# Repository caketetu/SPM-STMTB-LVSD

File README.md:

# STM32C092KBT6 Project

## 概要

STM32C092KBT6を使用した組み込み制御プロジェクト。

各種通信、タイマー、PWM、LED、モーター制御などの機能を実装する。

## 機能

* GPIO制御
* UART通信
* CAN通信
* タイマー割り込み
* PWM出力
* RGB LED制御
* Flashパラメータ保存

## ピン配置

| Pin  | Function  |
| ---- | --------- |
| PA11 | FDCAN1_RX |
| PB1  | FDCAN1_TX |
| PB7  | USART1_RX |
| PC14 | USART1_TX |
| PA8  | TIM1_CH1  |

## 開発環境

| 項目       | 内容                      |
| -------- | ----------------------- |
| MCU      | STM32C092KBT6           |
| IDE      | STM32CubeIDE for VSCode |
| CubeMX   | STM32CubeMX 6.15.0      |
| Firmware | STM32CubeC0             |
| Language | C                       |

## 実装予定機能

* [ ] CAN通信
* [ ] モーター制御
* [ ] 加減速制御
* [ ] Flashパラメータ管理
* [ ] RGB LED制御
* [ ] エラー処理
* [ ] ウォッチドッグ

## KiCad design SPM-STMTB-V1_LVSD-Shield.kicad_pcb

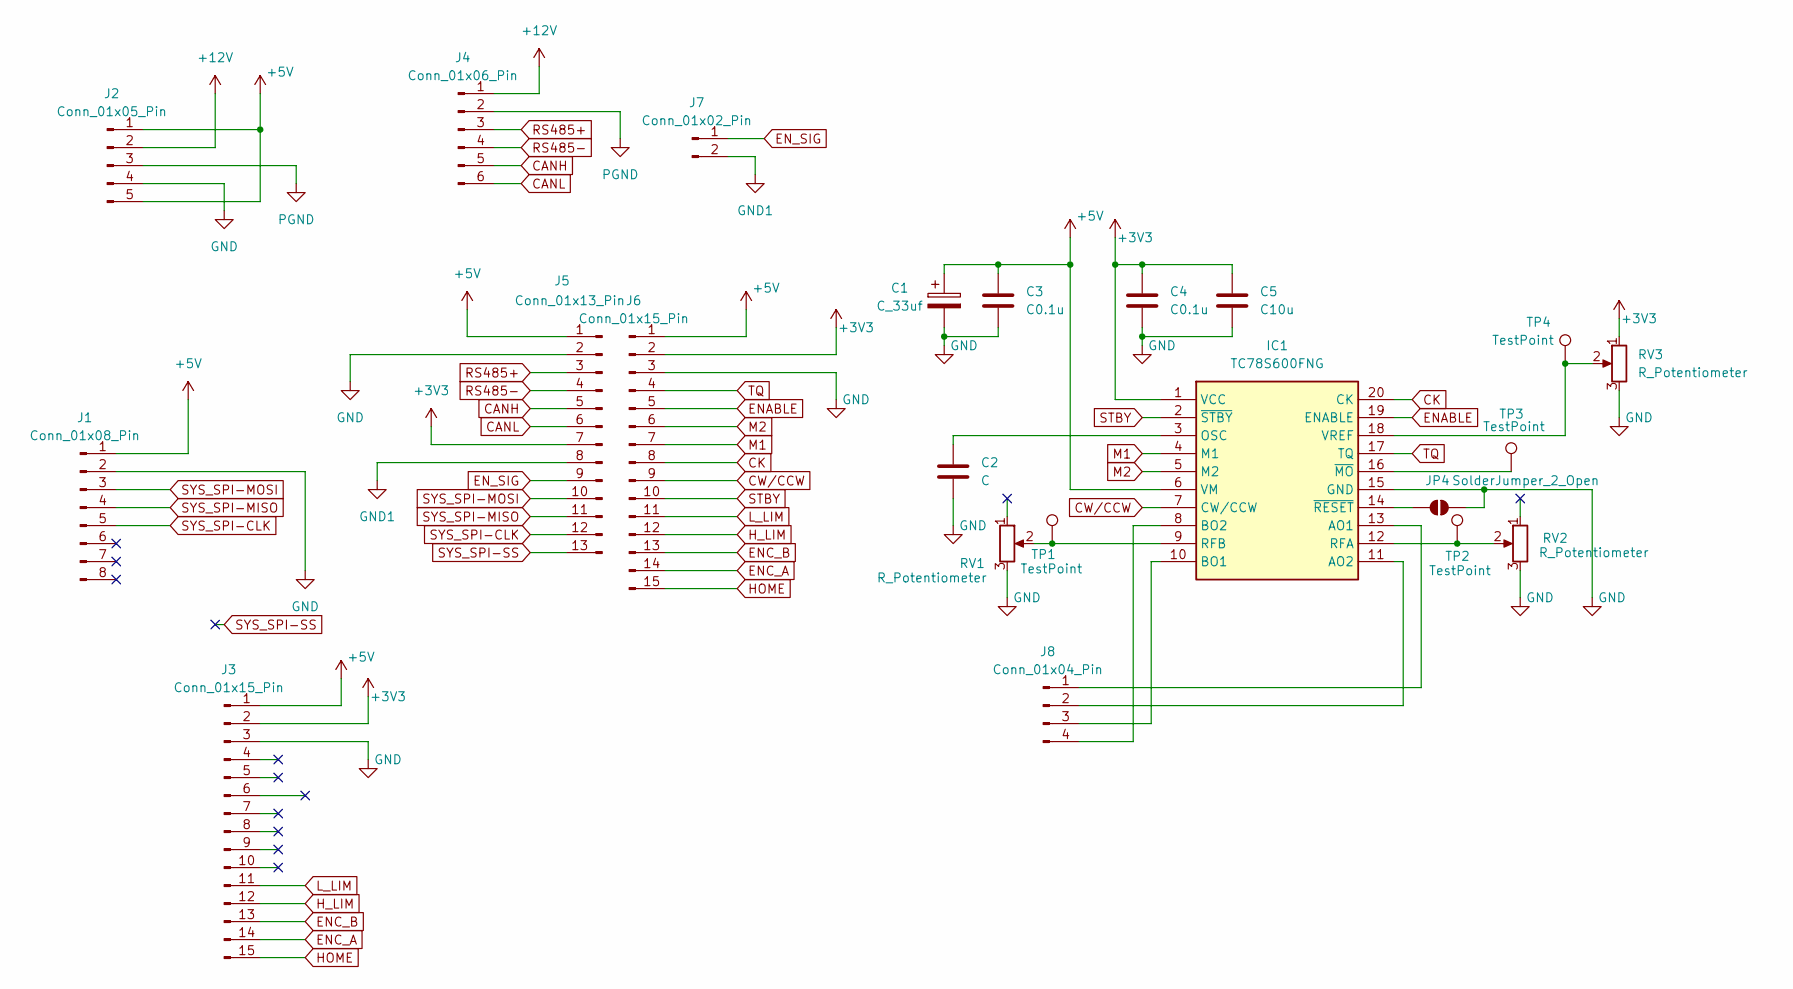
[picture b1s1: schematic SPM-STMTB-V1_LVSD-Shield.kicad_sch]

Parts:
C1: C_33uf; CP_Radial_D4.0mm_P1.50mm
C2: C; C_0402_1005Metric_Pad0.74x0.62mm_HandSolder
C3, C4: C0.1u; C_0603_1608Metric_Pad1.08x0.95mm_HandSolder
C5: C10u; C_1206_3216Metric_Pad1.33x1.80mm_HandSolder
IC1: TC78S600FNG; SOP65P640X160-20N; Manufacturer_Part_Number TC78S600FNG
J1: Conn_01x08_Pin; PinSocket_1x08_P2.54mm_Vertical
J2: Conn_01x05_Pin; PinSocket_1x05_P2.54mm_Vertical
J3, J6: Conn_01x15_Pin; PinSocket_1x15_P2.54mm_Vertical
J4: Conn_01x06_Pin; PinHeader_1x06_P2.54mm_Vertical
J5: Conn_01x13_Pin; PinSocket_1x13_P2.54mm_Vertical
J7: Conn_01x02_Pin; PinSocket_1x02_P2.54mm_Vertical
J8: Conn_01x04_Pin; PinSocket_1x04_P2.54mm_Vertical
JP4: SolderJumper_2_Open; SolderJumper-2_P1.3mm_Open_Pad1.0x1.5mm
RV1, RV2, RV3: R_Potentiometer; Potentiometer_Bourns_3296W_Vertical
TP1, TP2, TP3, TP4: TestPoint; TestPoint_Pad_1.0x1.0mm

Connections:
+3V3: C4.1, C5.1, IC1.1 (VCC), J3.2, J5.7, J6.2, RV3.1
+5V: C1.1, C3.1, IC1.6 (VM), J1.1, J2.1, J2.5, J3.1, J5.1, J6.1
+12V: J2.2, J4.1
CANH: J4.5, J5.5
CANL: J4.6, J5.6
CK: IC1.20 (CK), J6.8
CW/CCW: IC1.7 (CW/CCW), J6.9
ENABLE: IC1.19 (ENABLE), J6.5
ENC_A: J3.14, J6.14
ENC_B: J3.13, J6.13
EN_SIG: J5.9, J7.1
GND: C1.2, C2.2, C3.2, C4.2, C5.2, IC1.15 (GND), J1.2, J2.4, J3.3, J5.2, J6.3, JP4.2 (B), RV1.3, RV2.3, RV3.3
GND1: J5.8, J7.2
HOME: J3.15, J6.15
H_LIM: J3.12, J6.12
L_LIM: J3.11, J6.11
M1: IC1.4 (M1), J6.7
M2: IC1.5 (M2), J6.6
unnamed: IC1.13 (AO1), J8.1
unnamed: IC1.11 (AO2), J8.2
unnamed: IC1.10 (BO1), J8.3
unnamed: IC1.8 (BO2), J8.4
unnamed: C2.1, IC1.3 (OSC)
unnamed: IC1.12 (RFA), RV2.2, TP2.1
unnamed: IC1.9 (RFB), RV1.2, TP1.1
unnamed: IC1.18 (VREF), RV3.2, TP4.1
unnamed: IC1.16 (~MO), TP3.1
unnamed: IC1.14 (~RESET), JP4.1 (A)
PGND: J2.3, J4.2
RS485+: J4.3, J5.3
RS485-: J4.4, J5.4
STBY: IC1.2 (~STBY), J6.10
SYS_SPI-CLK: J1.5, J5.12
SYS_SPI-MISO: J1.4, J5.11
SYS_SPI-MOSI: J1.3, J5.10
SYS_SPI-SS: J5.13
TQ: IC1.17 (TQ), J6.4

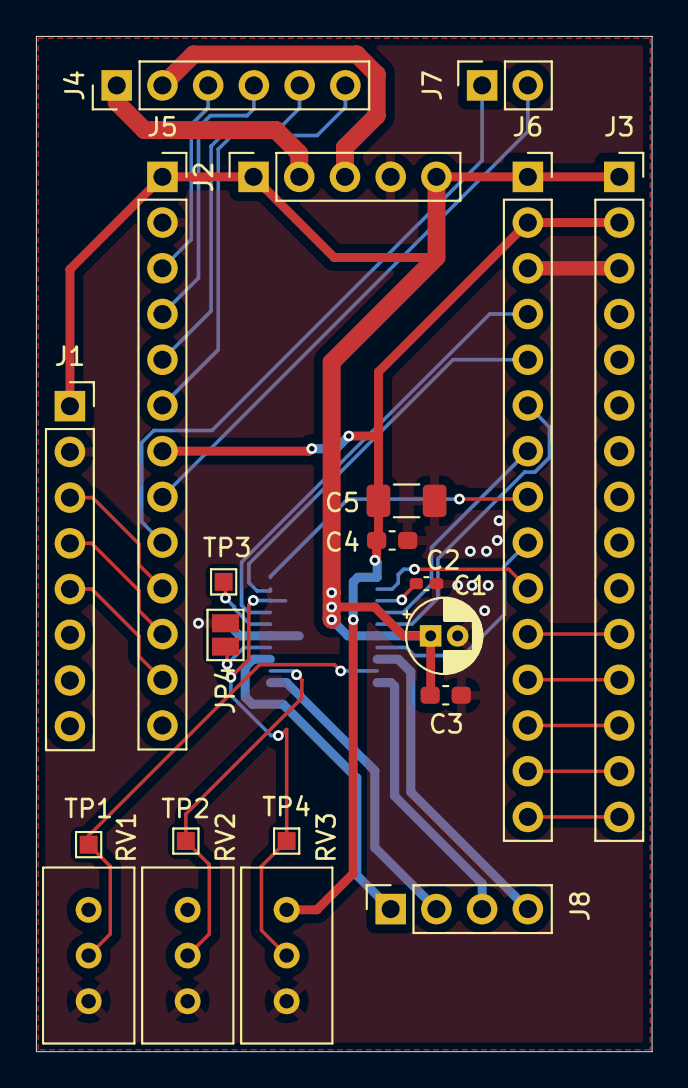
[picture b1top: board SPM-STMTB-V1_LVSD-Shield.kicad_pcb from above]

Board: 2 copper layers, 34.2 x 56.4 mm, 22 parts (1 on the bottom side), 36 nets.
